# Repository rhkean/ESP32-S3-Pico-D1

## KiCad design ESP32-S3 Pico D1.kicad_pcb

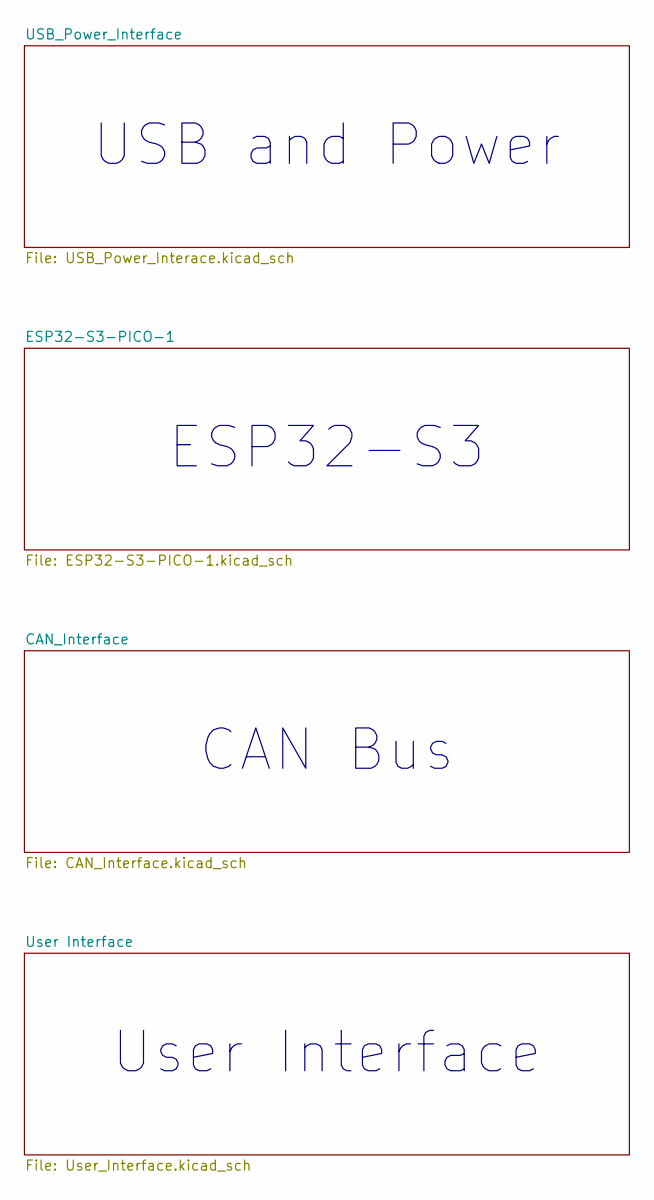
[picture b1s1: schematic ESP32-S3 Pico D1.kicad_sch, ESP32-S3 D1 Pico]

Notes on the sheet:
ESP32-S3
User Interface
USB and Power
CAN Bus

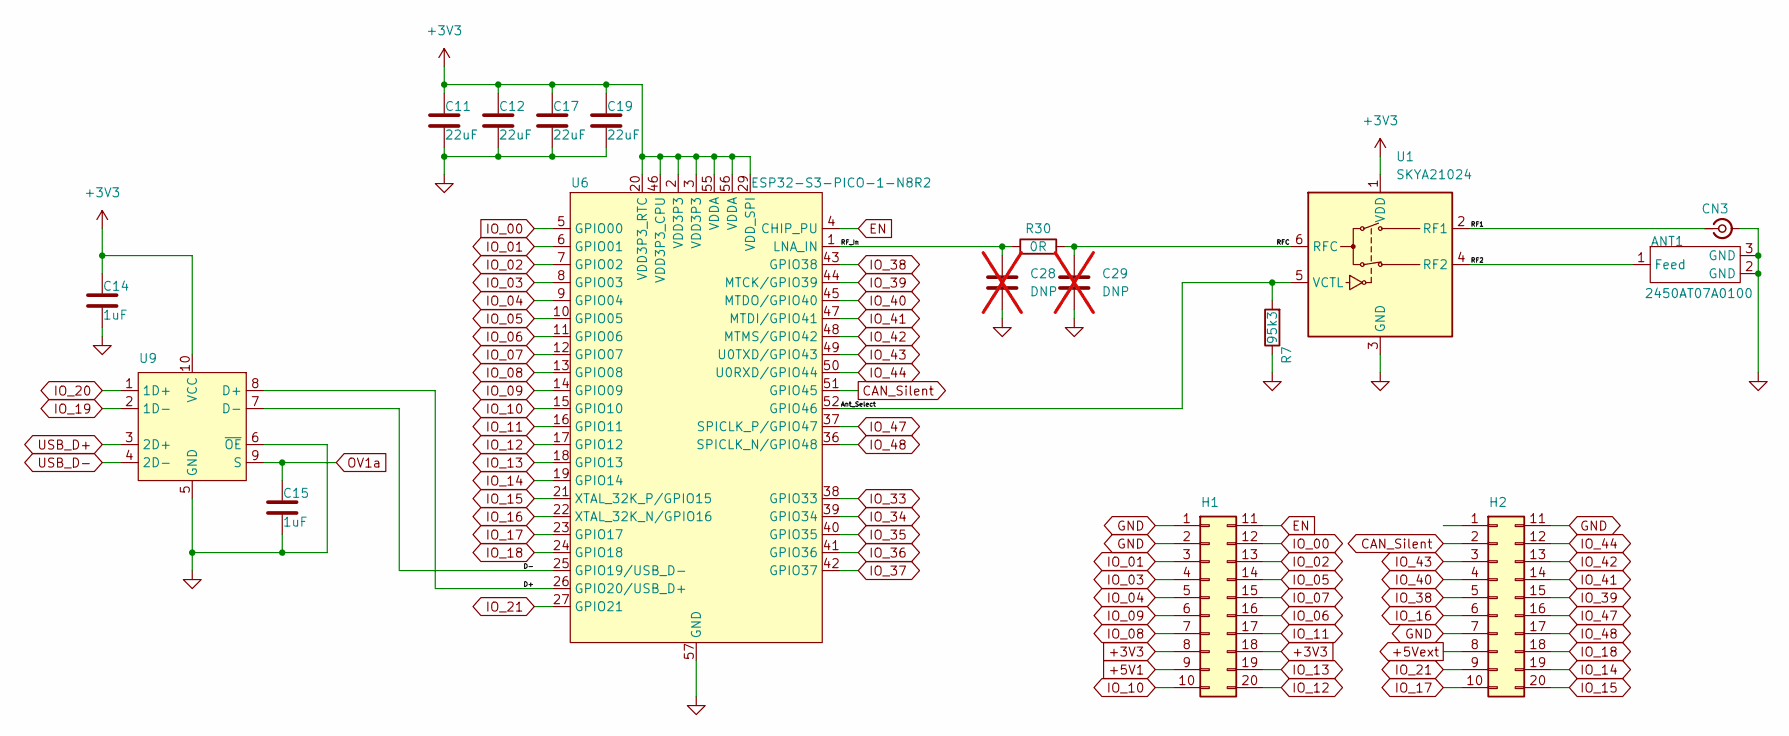
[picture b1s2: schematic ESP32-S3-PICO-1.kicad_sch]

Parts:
ANT1: 2450AT07A0100; Chip Antenna 0402; Manufacturer Part Number 2450AT07A0100; LCSC C17531353
C11, C12, C17, C19: 22uF; C0402_Dense; Manufacturer Part Number GRM158R61A226ME15D; LCSC C3845593
C14, C15: 1uF; C0201_Dense; Manufacturer Part Number CL03A105MO3NRNH; LCSC C307385
C28, C29: DNP; C0201_Dense; not fitted
CN3: 2337019-1; u.FL_Male_Pin_Coax_SMD; Manufacturer Part Number 2337019-1; LCSC C434807
H1, H2: ESP_Header; PinHeader_2x10_P2.54mm_Vertical
R7: 95k3; R0201_Dense; Manufacturer Part Number 0201WMF9532TEE; LCSC C423395
R30: 0R; R0201_Dense; Manufacturer Part Number RC0201FR-070RL; LCSC C106227
U1: SKYA21024; Manufacturer Part Number SKYA21024; LCSC C3304177
U6: ESP32-S3-PICO-1-N8R2; ESP32-S3-Pico-1; Manufacturer Part Number ESP32-S3-PICO-1-N8R2; LCSC C7558093
U9: TS3USB221A-Q1; Texas_UQFN-10_1.5x2mm_P0.5mm; Manufacturer Part Number TS3USB221AQRSERQ1; LCSC C181564

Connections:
+3V3: C11.1, C12.1, C14.1, C17.1, C19.1, H1.8, H1.18, U1.1 (VDD), U6.2 (VDD3P3), U6.3 (VDD3P3), U6.20 (VDD3P3_RTC), U6.29 (VDD_SPI), U6.46 (VDD3P3_CPU), U6.55 (VDDA), U6.56 (VDDA), U9.10 (VCC); also elsewhere on the board
+5V1: H1.9; also elsewhere on the board
+5Vext: H2.8; also elsewhere on the board
/ESP32-S3-PICO-1/Ant_Select: R7.2, U1.5 (VCTL), U6.52 (GPIO46)
/ESP32-S3-PICO-1/D+: U6.26 (GPIO20/USB_D+), U9.8 (D+)
/ESP32-S3-PICO-1/D-: U6.25 (GPIO19/USB_D-), U9.7 (D-)
/ESP32-S3-PICO-1/RF1: CN3.1 (In), U1.2 (RF1)
/ESP32-S3-PICO-1/RF2: ANT1.1 (Feed), ANT1.4 (Feed), U1.4 (RF2)
/ESP32-S3-PICO-1/RFC: C29.1, R30.2, U1.6 (RFC)
/ESP32-S3-PICO-1/RF_In: C28.1, R30.1, U6.1 (LNA_IN)
CAN_Silent: H2.2, U6.51 (GPIO45); also elsewhere on the board
EN: H1.11, U6.4 (CHIP_PU); also elsewhere on the board
GND: ANT1.2 (GND), ANT1.3 (GND), C11.2, C12.2, C14.2, C15.2, C17.2, C19.2, C28.2, C29.2, CN3.2 (Ext), H1.1, H1.2, H2.7, H2.11, R7.1, U1.3 (GND), U6.57 (GND), U9.5 (GND), U9.6 (~OE); also elsewhere on the board
IO_00: H1.12, U6.5 (GPIO00); also elsewhere on the board
IO_01: H1.3, U6.6 (GPIO01)
IO_02: H1.13, U6.7 (GPIO02); also elsewhere on the board
IO_03: H1.4, U6.8 (GPIO03)
IO_04: H1.5, U6.9 (GPIO04)
IO_05: H1.14, U6.10 (GPIO05)
IO_06: H1.16, U6.11 (GPIO06)
IO_07: H1.15, U6.12 (GPIO07)
IO_08: H1.7, U6.13 (GPIO08)
IO_09: H1.6, U6.14 (GPIO09)
IO_10: H1.10, U6.15 (GPIO10)
IO_11: H1.17, U6.16 (GPIO11)
IO_12: H1.20, U6.17 (GPIO12)
IO_13: H1.19, U6.18 (GPIO13)
IO_14: H2.19, U6.19 (GPIO14)
IO_15: H2.20, U6.21 (XTAL_32K_P/GPIO15)
IO_16: H2.6, U6.22 (XTAL_32K_N/GPIO16)
IO_17: H2.10, U6.23 (GPIO17)
IO_18: H2.18, U6.24 (GPIO18)
IO_19: U9.2 (1D-)
IO_20: U9.1 (1D+)
IO_21: H2.9, U6.27 (GPIO21)
IO_33: U6.38 (GPIO33)
IO_34: U6.39 (GPIO34)
IO_35: U6.40 (GPIO35)
IO_36: U6.41 (GPIO36)
IO_37: U6.42 (GPIO37)
IO_38: H2.5, U6.43 (GPIO38)
IO_39: H2.15, U6.44 (MTCK/GPIO39)
IO_40: H2.4, U6.45 (MTDO/GPIO40)
IO_41: H2.14, U6.47 (MTDI/GPIO41)
IO_42: H2.13, U6.48 (MTMS/GPIO42)
IO_43: H2.3, U6.49 (U0TXD/GPIO43)
IO_44: H2.12, U6.50 (U0RXD/GPIO44)
IO_47: H2.16, U6.37 (SPICLK_P/GPIO47); also elsewhere on the board
IO_48: H2.17, U6.36 (SPICLK_N/GPIO48); also elsewhere on the board
OV1a: C15.1, U9.9 (S); also elsewhere on the board
USB_D+: U9.3 (2D+); also elsewhere on the board
USB_D-: U9.4 (2D-); also elsewhere on the board

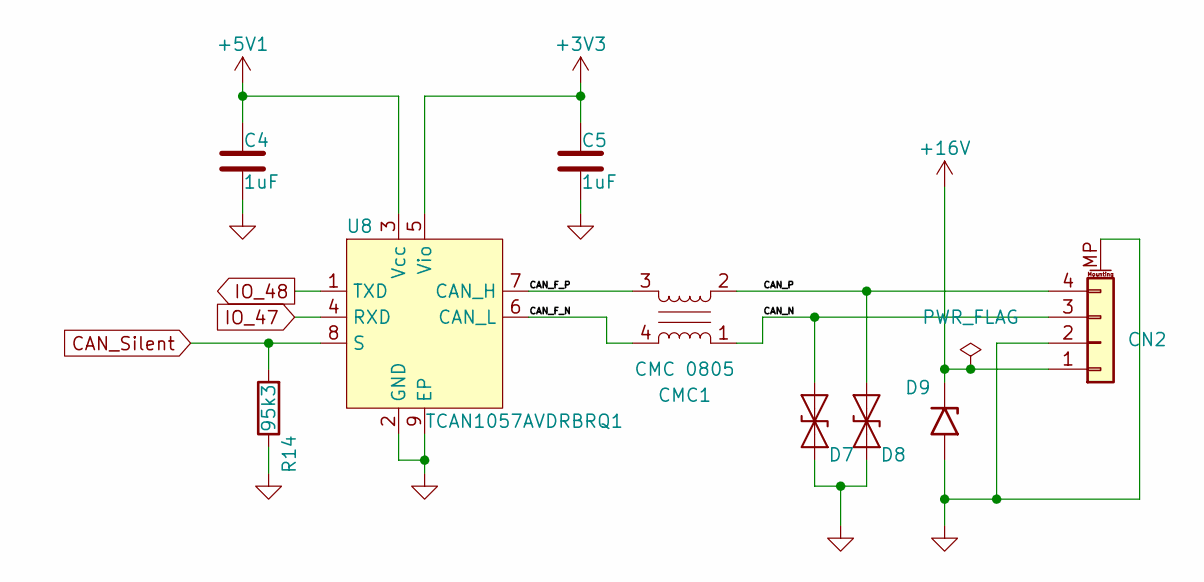
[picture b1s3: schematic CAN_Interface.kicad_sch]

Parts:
C4, C5: 1uF; C0201_Dense; Manufacturer Part Number CL03A105MO3NRNH; LCSC C307385
CMC1: CMC 0805; CMC_0805; Manufacturer Part Number ACM2012H-900-2P-T03; LCSC C448605
CN2: BM04B-ACHSS; JST_ACH_BM04B-ACHSS-A-GAN-ETF_1x04-1MP_P1.20mm_Vertical; Manufacturer Part Number WAFER-ACH1.2-4PWB; LCSC C46772640
D7, D8: ESDSLC24VLB-TP; DFN1006-2; Manufacturer Part Number ESDSLC24VLB-TP; LCSC C7463931
D9: D15V0H1U2LP-7B; DFN1006-2; Manufacturer Part Number D15V0H1U2LP-7B; LCSC C1973850
R14: 95k3; R0201_Dense; Manufacturer Part Number 0201WMF9532TEE; LCSC C423395
U8: TCAN1057AVDRBRQ1; VSON-8-1EP_3x3mm_P0.65mm_EP1.65x2.4mm_ThermalVias; Manufacturer Part Number TCAN1057AVDRBRQ1; LCSC C3234121

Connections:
+3V3: C5.1, U8.5 (Vio); also elsewhere on the board
+5V1: C4.1, U8.3 (Vcc); also elsewhere on the board
+16V: CN2.1 (GND), D9.1 (A1); also elsewhere on the board
/CAN_Interface/CAN_F_N: CMC1.4, U8.6 (CAN_L)
/CAN_Interface/CAN_F_P: CMC1.3, U8.7 (CAN_H)
/CAN_Interface/CAN_N: CMC1.1, CN2.3 (CAN_L), D7.1 (A1)
/CAN_Interface/CAN_P: CMC1.2, CN2.4 (CAN_H), D8.1 (A1)
CAN_Silent: R14.2, U8.8 (S); also elsewhere on the board
GND: C4.2, C5.2, CN2.2 (+12V), CN2.MP (MountPin), D7.2 (A2), D8.2 (A2), D9.2 (A2), R14.1, U8.2 (GND), U8.9 (EP); also elsewhere on the board
IO_47: U8.4 (RXD); also elsewhere on the board
IO_48: U8.1 (TXD); also elsewhere on the board

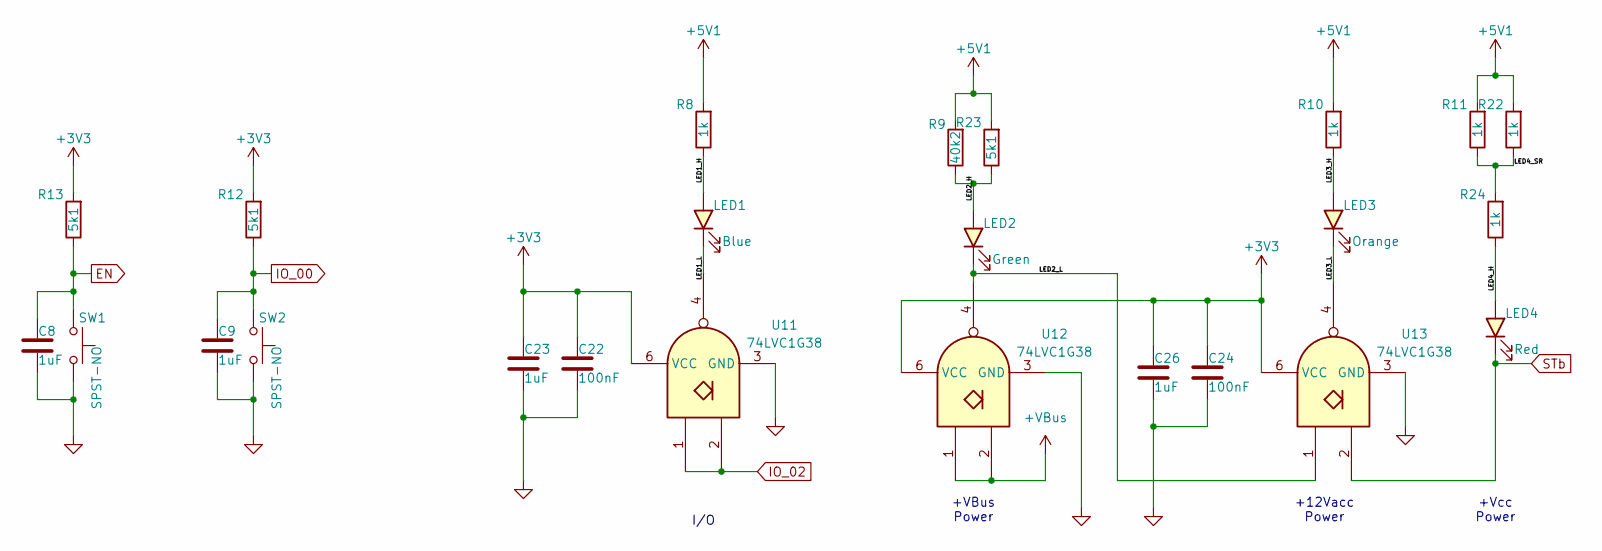
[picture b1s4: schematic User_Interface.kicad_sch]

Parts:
C8, C9, C23, C26: 1uF; C0201_Dense; Manufacturer Part Number CL03A105MO3NRNH; LCSC C307385
C22, C24: 100nF; C0201_Dense; Manufacturer Part Number GRM033R61E104KE14D; LCSC C76939
LED1: Blue; LED_0201-2; Manufacturer Part Number XL-0201UBC; LCSC C3646921
LED2: Green; LED_0201-2; Manufacturer Part Number XL-0201UGC; LCSC C3646922
LED3: Orange; LED_0201-2; Manufacturer Part Number XL-0201UOC; LCSC C5440629
LED4: Red; LED_0201-2; Manufacturer Part Number XL-0201SURC; LCSC C3646923
R8, R10, R11, R22, R24: 1k; R0201_Dense; Manufacturer Part Number 0201WMF1001TEE; LCSC C270365
R9: 40k2; R0201_Dense; Manufacturer Part Number 0201WMF4022TEE; LCSC C423536
R12, R13, R23: 5k1; R0201_Dense; Manufacturer Part Number 0201WMF5101TEE; LCSC C270344
SW1, SW2: SPST-NO; SW_SPST_B3U_series; Manufacturer Part Number B3U-3000P(M)-B; LCSC C4364471
U11, U12, U13: 74LVC1G38; DSF6; Manufacturer Part Number SN74LVC1G38DSFR; LCSC C2867531

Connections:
+3V3: C22.1, C23.1, C24.1, C26.1, R12.2, R13.2, U11.6 (VCC), U12.6 (VCC), U13.6 (VCC); also elsewhere on the board
+5V1: R8.2, R9.2, R10.2, R11.2, R22.2, R23.2; also elsewhere on the board
+VBus: U12.1, U12.2; also elsewhere on the board
/User Interface/LED1_H: LED1.2 (A), R8.1
/User Interface/LED1_L: LED1.1 (K), U11.4
/User Interface/LED2_H: LED2.2 (A), R9.1, R23.1
/User Interface/LED2_L: LED2.1 (K), U12.4, U13.1
/User Interface/LED3_H: LED3.2 (A), R10.1
/User Interface/LED3_L: LED3.1 (K), U13.4
/User Interface/LED4_H: LED4.2 (A), R24.1
/User Interface/LED4_SR: R11.1, R22.1, R24.2
EN: C8.1, R13.1, SW1.1; also elsewhere on the board
GND: C8.2, C9.2, C22.2, C23.2, C24.2, C26.2, SW1.2, SW2.2, U11.3 (GND), U12.3 (GND), U13.3 (GND); also elsewhere on the board
IO_00: C9.1, R12.1, SW2.1; also elsewhere on the board
IO_02: U11.1, U11.2; also elsewhere on the board
STb: LED4.1 (K), U13.2; also elsewhere on the board

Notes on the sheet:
+Vcc Power
+12Vacc Power
I/O
+VBus Power

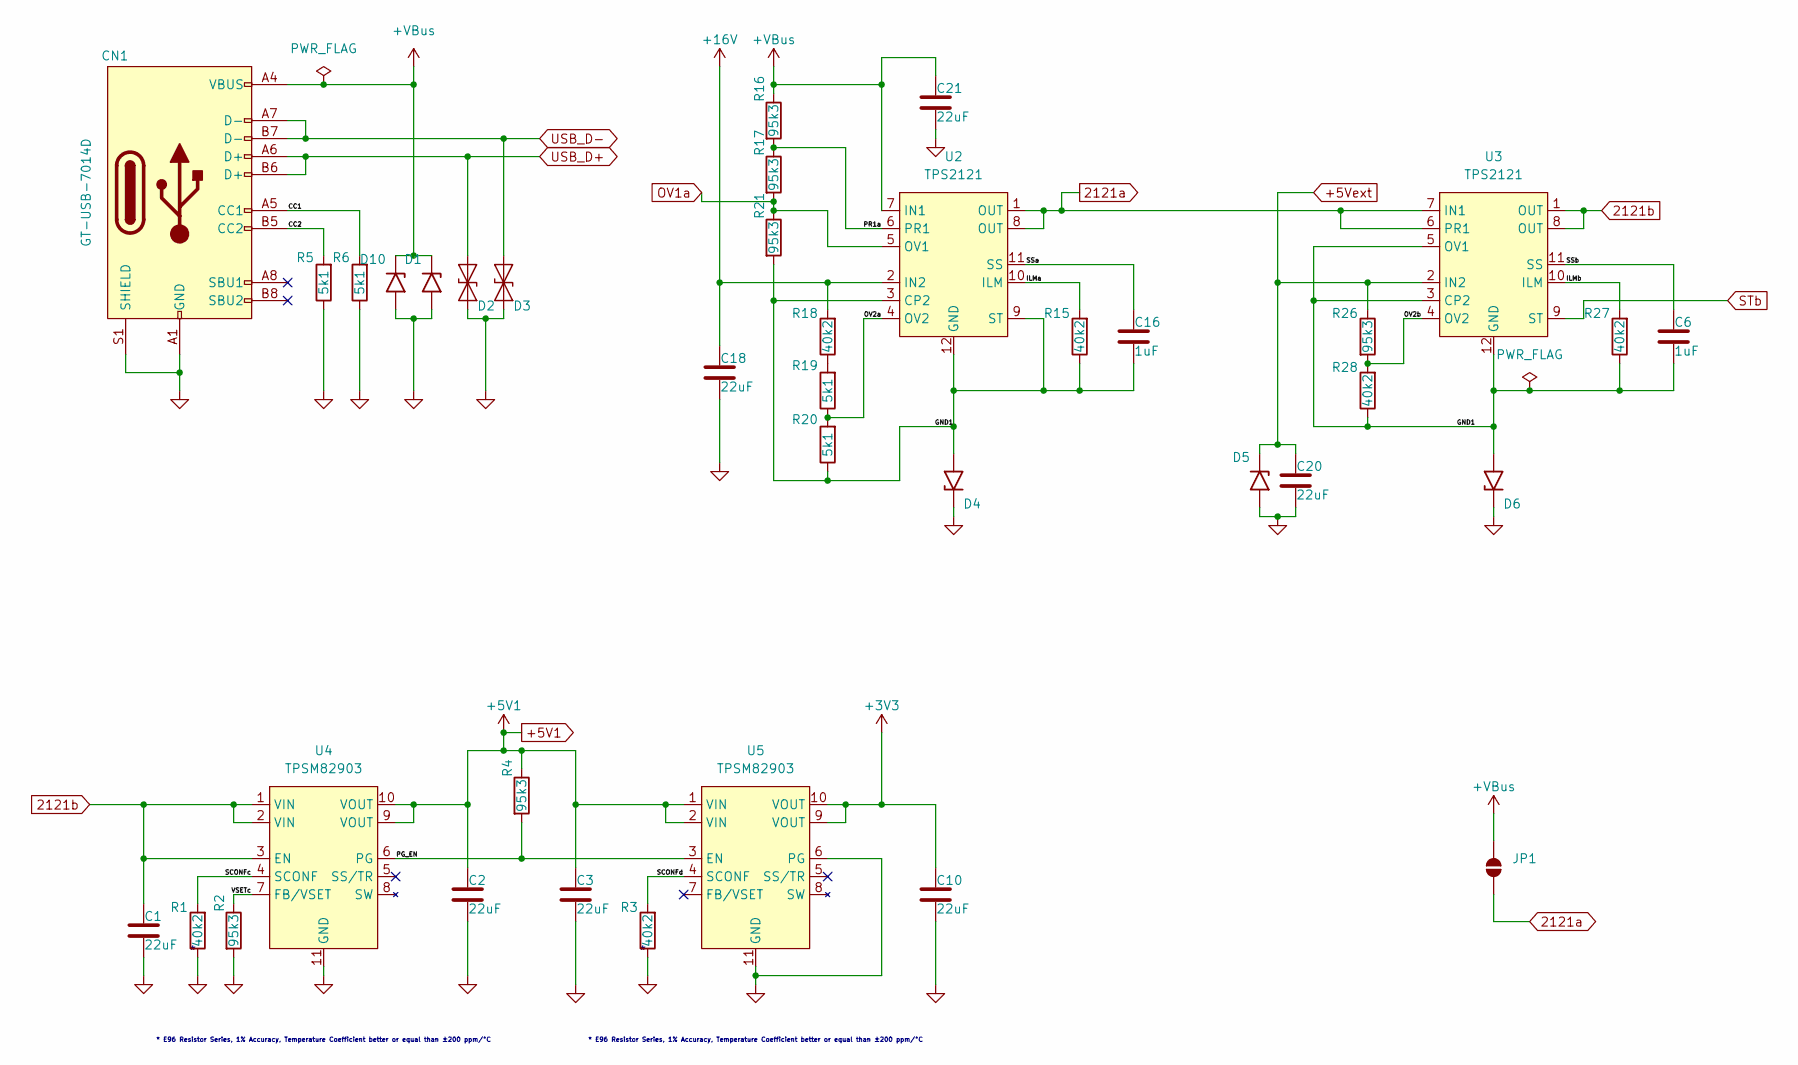
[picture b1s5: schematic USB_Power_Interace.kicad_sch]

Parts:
C1, C18: 22uF; C0603_Dense; Manufacturer Part Number GRM188C61E226ME01D; LCSC C29519229
C2, C3, C10, C20, C21: 22uF; C0402_Dense; Manufacturer Part Number GRM158R61A226ME15D; LCSC C3845593
C6, C16: 1uF; C0201_Dense; Manufacturer Part Number CL03A105MO3NRNH; LCSC C307385
CN1: GT-USB-7014D; USB_C_Receptacle_G-Switch-GT-USB-7014D; Manufacturer Part Number GT-USB-7014D; LCSC C2843969
D1, D4, D5, D6, D10: D15V0H1U2LP-7B; DFN1006-2; Manufacturer Part Number D15V0H1U2LP-7B; LCSC C1973850
D2, D3: ESDSLC24VLB-TP; DFN1006-2; Manufacturer Part Number ESDSLC24VLB-TP; LCSC C7463931
JP1: SolderJumper_2_Open; SolderJumper-2_Open
R1, R3, R15, R18, R27, R28: 40k2; R0201_Dense; Manufacturer Part Number 0201WMF4022TEE; LCSC C423536
R2, R4, R16, R17, R21, R26: 95k3; R0201_Dense; Manufacturer Part Number 0201WMF9532TEE; LCSC C423395
R5, R6, R19, R20: 5k1; R0201_Dense; Manufacturer Part Number 0201WMF5101TEE; LCSC C270344
U2, U3: TPS2121; VQHN-HR-12; Manufacturer Part Number TPS2121RUXR; LCSC C485916
U4, U5: TPSM82903; uSIP-11_3.0x2.8_ThermalVias; Manufacturer Part Number TPSM82903SISR; LCSC C6290583

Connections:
2121a: JP1.1 (A), U2.1 (OUT), U2.8 (OUT), U3.6 (PR1), U3.7 (IN1)
2121b: C1.1, U3.1 (OUT), U3.8 (OUT), U4.1 (VIN), U4.2 (VIN), U4.3 (EN)
+3V3: C10.1, U5.9 (VOUT), U5.10 (VOUT); also elsewhere on the board
+5V1: C2.1, C3.1, R4.1, U4.9 (VOUT), U4.10 (VOUT), U5.1 (VIN), U5.2 (VIN); also elsewhere on the board
+5Vext: C20.1, D5.1 (A1), R26.1, U3.2 (IN2); also elsewhere on the board
+16V: C18.1, R18.2, U2.2 (IN2); also elsewhere on the board
+VBus: C21.1, CN1.A4 (VBUS), CN1.A9 (VBUS), CN1.B4 (VBUS), CN1.B9 (VBUS), D1.1 (A1), D10.1 (A1), JP1.2 (B), R16.1, U2.7 (IN1); also elsewhere on the board
/USB_Power_Interface/CC1: CN1.A5 (CC1), R6.2
/USB_Power_Interface/CC2: CN1.B5 (CC2), R5.2
/USB_Power_Interface/GND1: C6.2, C16.2, D4.2 (A2), D6.2 (A2), R15.1, R20.1, R21.2, R27.1, R28.1, U2.3 (CP2), U2.9 (ST), U2.12 (GND), U3.3 (CP2), U3.5 (OV1), U3.12 (GND)
/USB_Power_Interface/ILMa: R15.2, U2.10 (ILM)
/USB_Power_Interface/ILMb: R27.2, U3.10 (ILM)
/USB_Power_Interface/OV2a: R19.1, R20.2, U2.4 (OV2)
/USB_Power_Interface/OV2b: R26.2, R28.2, U3.4 (OV2)
/USB_Power_Interface/PG_EN: R4.2, U4.6 (PG), U5.3 (EN)
/USB_Power_Interface/PR1a: R16.2, R17.1, U2.6 (PR1)
/USB_Power_Interface/SCONFc: R1.2, U4.4 (SCONF)
/USB_Power_Interface/SCONFd: R3.2, U5.4 (SCONF)
/USB_Power_Interface/SSa: C16.1, U2.11 (SS)
/USB_Power_Interface/SSb: C6.1, U3.11 (SS)
/USB_Power_Interface/VSETc: R2.1, U4.7 (FB/VSET)
GND: C1.2, C2.2, C3.2, C10.2, C18.2, C20.2, C21.2, CN1.A1 (GND), CN1.A12 (GND), CN1.B1 (GND), CN1.B12 (GND), CN1.S1 (SHIELD), CN1.S2 (SHIELD), CN1.S3 (SHIELD), CN1.S4 (SHIELD), D1.2 (A2), D2.2 (A2), D3.2 (A2), D4.1 (A1), D5.2 (A2), D6.1 (A1), D10.2 (A2), R1.1, R2.2, R3.1, R5.1, R6.1, U4.11 (GND), U5.6 (PG), U5.11 (GND); also elsewhere on the board
unnamed: R18.1, R19.2
OV1a: R17.2, R21.1, U2.5 (OV1); also elsewhere on the board
STb: U3.9 (ST); also elsewhere on the board
USB_D+: CN1.A6 (D+), CN1.B6 (D+), D2.1 (A1); also elsewhere on the board
USB_D-: CN1.A7 (D-), CN1.B7 (D-), D3.1 (A1); also elsewhere on the board

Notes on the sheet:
* E96 Resistor Series, 1% Accuracy, Temperature Coefficient better or equal than ±200 ppm/°C

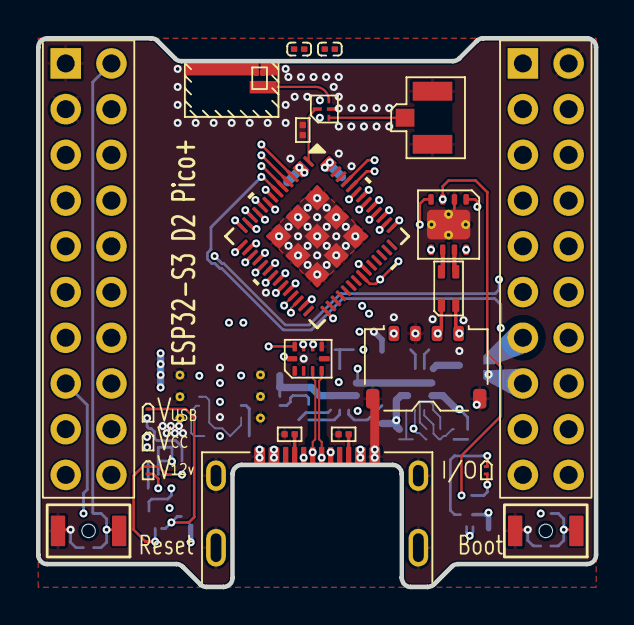
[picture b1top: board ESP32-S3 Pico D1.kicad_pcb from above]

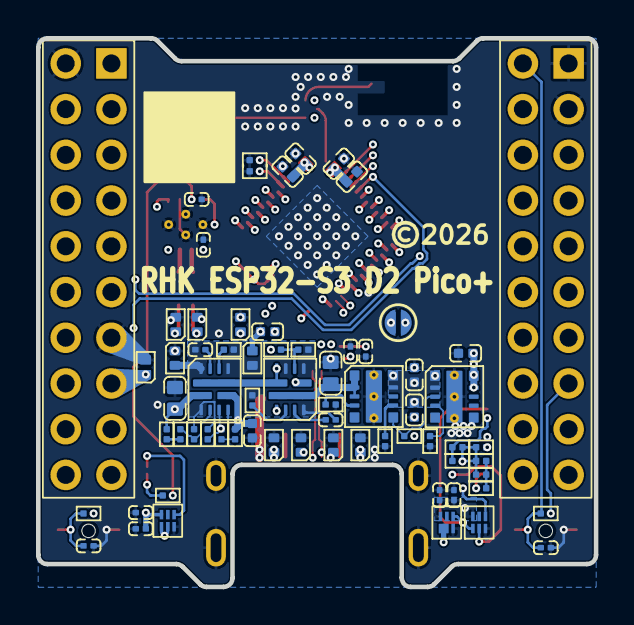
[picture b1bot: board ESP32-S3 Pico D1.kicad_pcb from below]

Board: 6 copper layers, 31.0 x 30.5 mm, 88 parts (66 on the bottom side), 77 nets.

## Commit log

2026-02-12 successful 1st pass, but I want to try some new bus'ing techniques to clean up the routing
2026-02-21 Update CAN_Interface.kicad_sch, ESP32-S3 Pico D1.kicad_dru, ESP32-S3 Pico D1.kicad_pcb, and 5 more files reroute completed

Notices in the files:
ESP32-S3 Pico D1.kicad_pcb:
©2026
